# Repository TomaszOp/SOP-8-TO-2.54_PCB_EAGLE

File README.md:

# SOP-8 to raster 2.54 mm PCB EAGLE

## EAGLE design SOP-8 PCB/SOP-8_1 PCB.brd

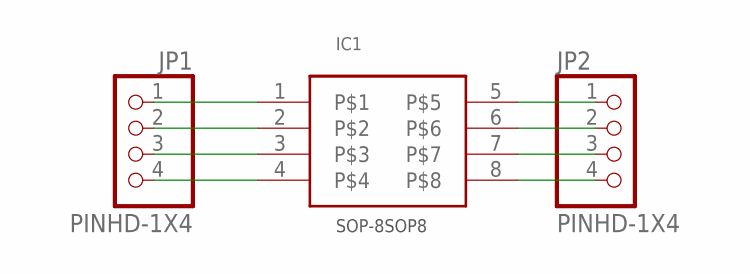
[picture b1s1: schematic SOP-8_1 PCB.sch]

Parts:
IC1: SOP-8SOP8; SOP-8
JP1, JP2: PINHD-1X4; 1X04

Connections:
unnamed: IC1.1, JP1.1
unnamed: IC1.2, JP1.2
unnamed: IC1.3, JP1.3
unnamed: IC1.4, JP1.4
unnamed: IC1.5, JP2.1
unnamed: IC1.6, JP2.2
unnamed: IC1.7, JP2.3
unnamed: IC1.8, JP2.4

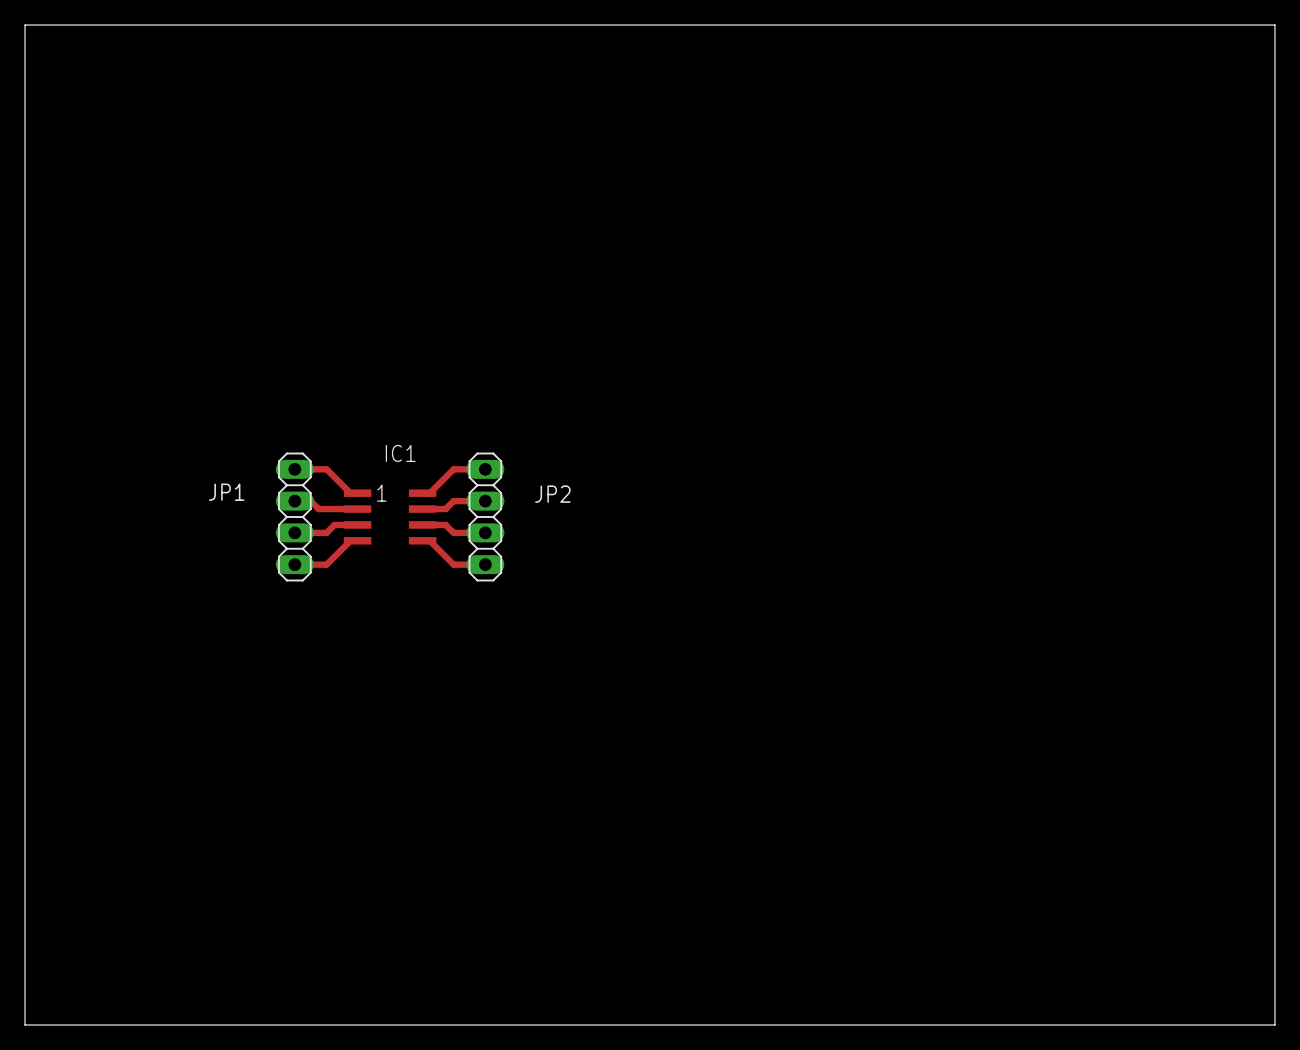
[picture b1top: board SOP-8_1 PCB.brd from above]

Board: 2 copper layers, 100.0 x 80.0 mm, 3 parts (0 on the bottom side), 8 nets.

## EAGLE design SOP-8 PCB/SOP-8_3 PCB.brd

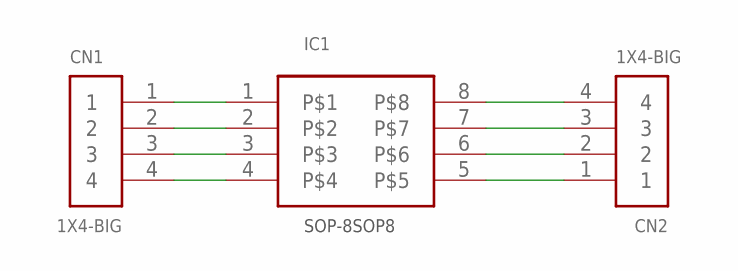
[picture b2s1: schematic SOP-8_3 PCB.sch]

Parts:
CN1, CN2: 1X4-BIG; 1X04-BIG
IC1: SOP-8SOP8; SOP-8

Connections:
unnamed: CN1.1, IC1.1
unnamed: CN1.2, IC1.2
unnamed: CN1.3, IC1.3
unnamed: CN1.4, IC1.4
unnamed: CN2.4, IC1.8
unnamed: CN2.3, IC1.7
unnamed: CN2.2, IC1.6
unnamed: CN2.1, IC1.5

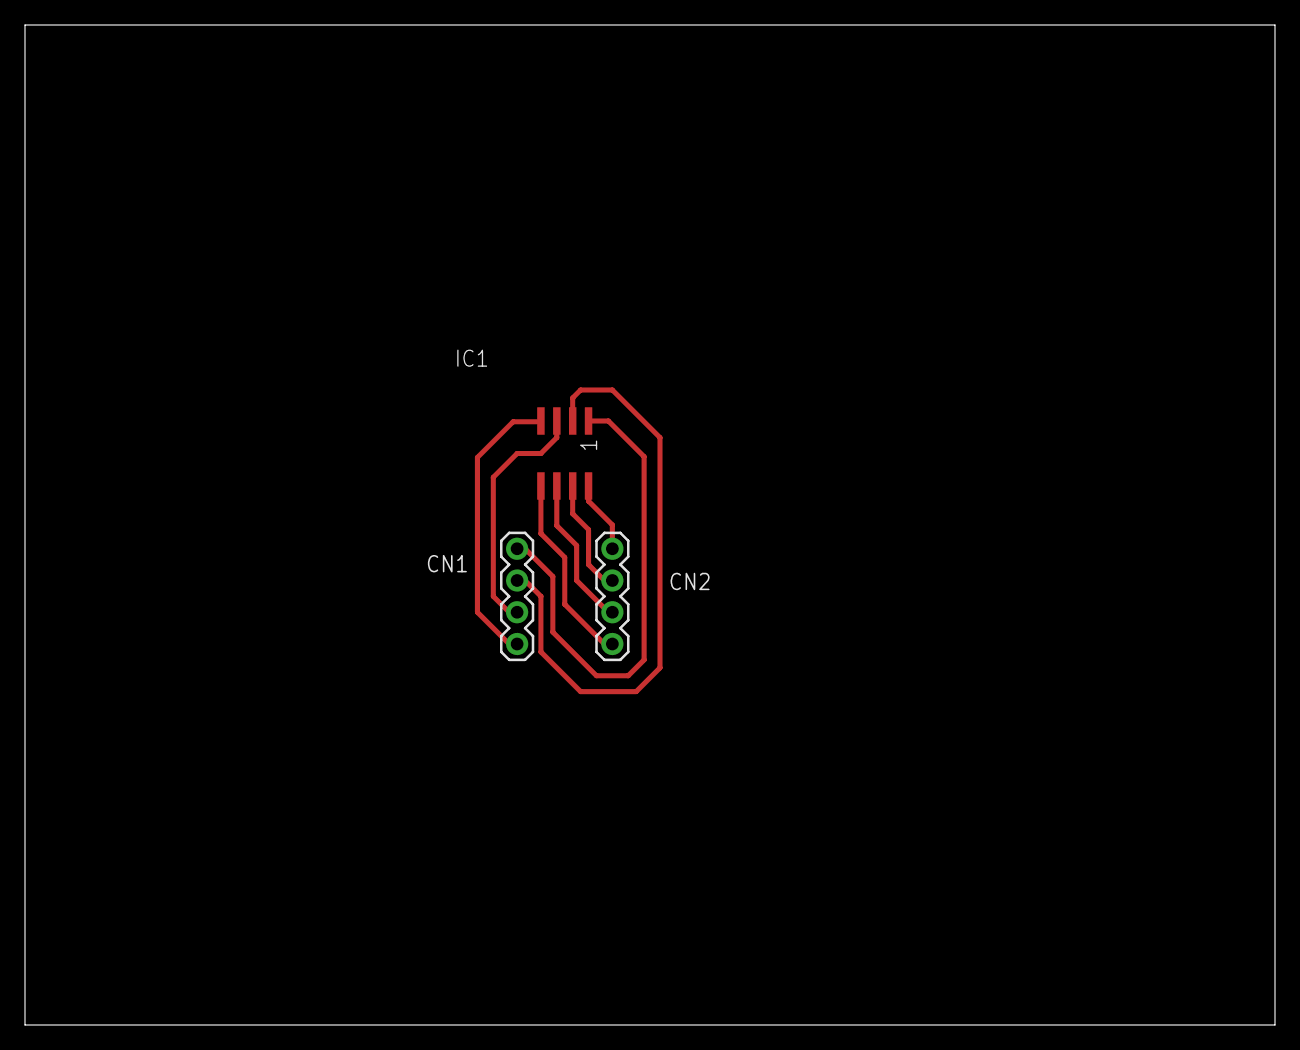
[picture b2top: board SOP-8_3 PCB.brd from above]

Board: 2 copper layers, 100.0 x 80.0 mm, 3 parts (0 on the bottom side), 8 nets.
